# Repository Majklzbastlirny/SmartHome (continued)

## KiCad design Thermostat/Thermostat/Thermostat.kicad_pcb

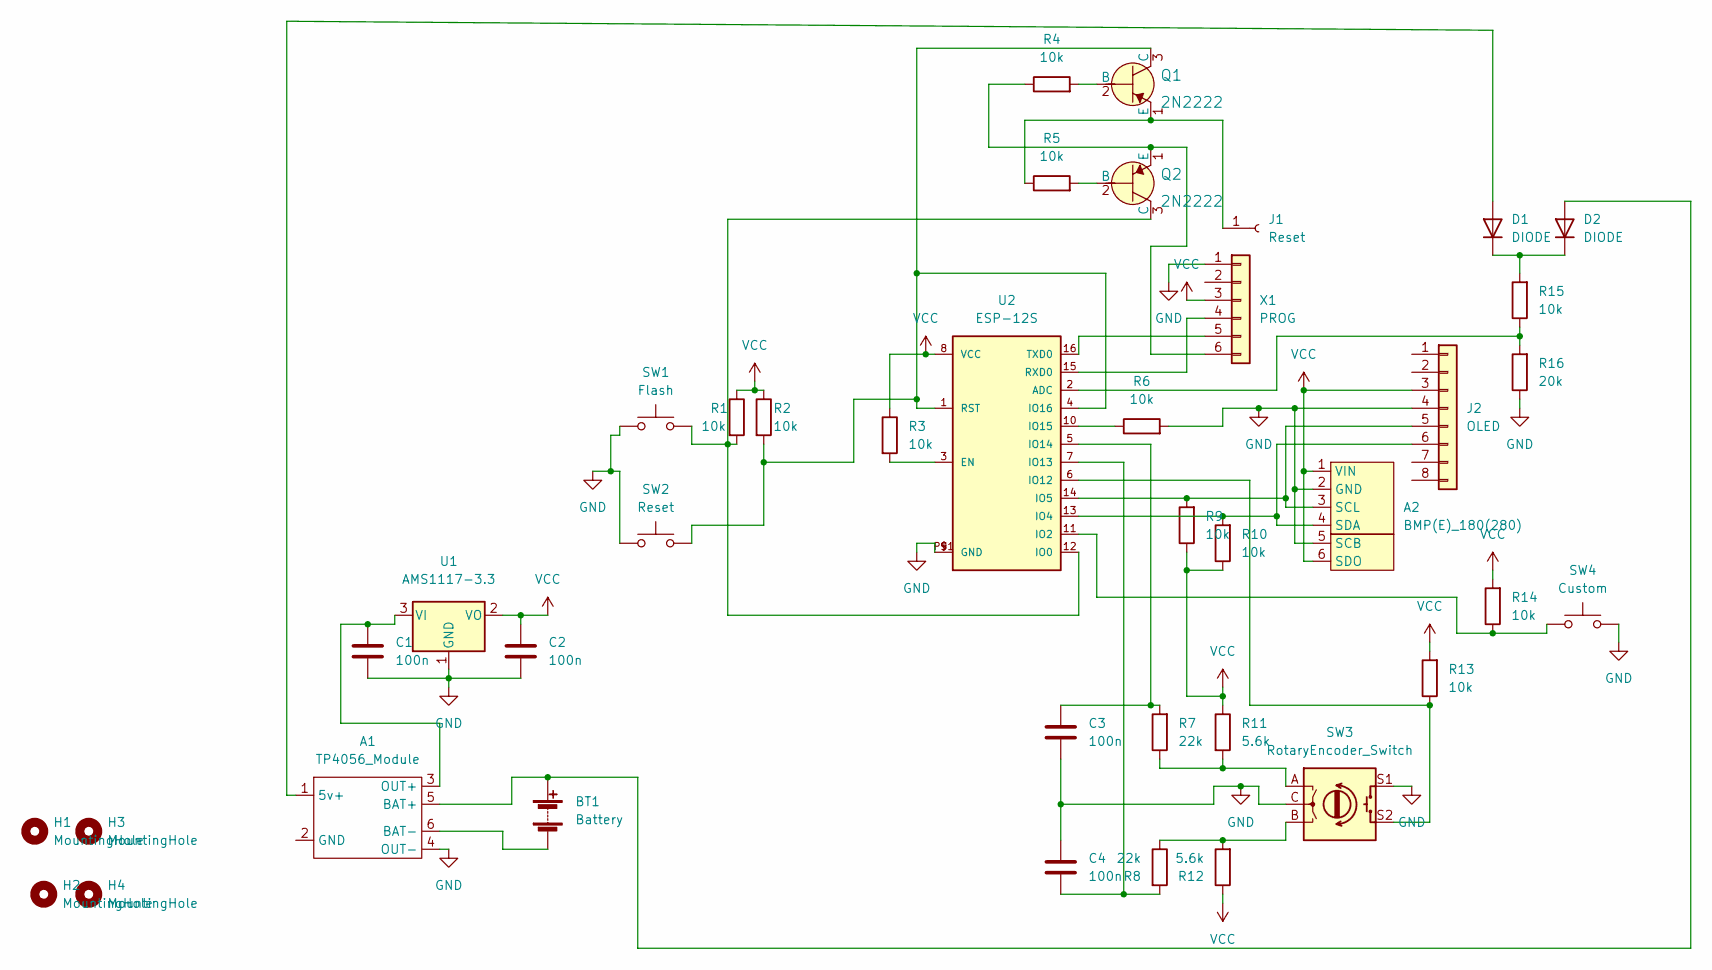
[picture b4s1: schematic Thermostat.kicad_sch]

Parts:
A1: TP4056_Module; TP4056-18650
A2: BMP(E)_180(280); PinHeader_1x06_P2.54mm_Vertical
BT1: Battery; BatteryHolder_MPD_BH-18650-PC2
C1, C2, C3, C4: 100n; C_Disc_D7.5mm_W2.5mm_P5.00mm
D1, D2: DIODE; D_DO-34_SOD68_P10.16mm_Horizontal
H1, H2, H3, H4: MountingHole; MountingHole_3.2mm_M3_DIN965_Pad_TopBottom
J1: Reset; PinHeader_1x01_P2.54mm_Vertical
J2: OLED; Adafruit_SSD1306
Q1, Q2: 2N2222; TO-18-3; MPN 2N2222; Digi-Key_PN 2N2222CS-ND
R1, R2, R3, R4, R5, R6, R9, R10, R13, R14, R15: 10k; R_Axial_DIN0207_L6.3mm_D2.5mm_P10.16mm_Horizontal
R7, R8: 22k; R_Axial_DIN0207_L6.3mm_D2.5mm_P10.16mm_Horizontal
R11, R12: 5.6k; R_Axial_DIN0207_L6.3mm_D2.5mm_P10.16mm_Horizontal
R16: 20k; R_Axial_DIN0207_L6.3mm_D2.5mm_P10.16mm_Horizontal
SW1: Flash; SW_PUSH_6mm
SW2: Reset; SW_PUSH_6mm
SW3: RotaryEncoder_Switch; RotaryEncoder_Alps_EC11E-Switch_Vertical_H20mm_CircularMoun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
SW4: Custom; SW_PUSH_6mm
U1: AMS1117-3.3; SOT-223-3_TabPin2
U2: ESP-12S
X1: PROG; PinHeader_1x06_P2.54mm_Vertical

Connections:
GND: A1.4 (OUT-), A2.2 (GND), A2.5 (SCB), C1.2, C2.2, C3.2, C4.1, J2.4, R6.2, R16.1, SW1.1, SW2.1, SW3.C, SW3.S1, SW4.2, U1.1 (GND), U2.9 (GND), U2.P$1 (GND), X1.1
unnamed: A1.1 (5v+), D1.1 (A)
unnamed: A1.3 (OUT+), C1.1, U1.3 (VI)
unnamed: A1.5 (BAT+), BT1.1 (+), D2.1 (A)
unnamed: A1.6 (BAT-), BT1.2 (-)
unnamed: A2.3 (SCL), J2.5, R9.2, U2.14 (IO5)
unnamed: A2.4 (SDA), J2.6, R10.2, U2.13 (IO4)
unnamed: C3.1, R7.2, U2.5 (IO14)
unnamed: C4.2, R8.2, U2.7 (IO13)
unnamed: D1.2 (K), D2.2 (K), R15.2
unnamed: J1.1, Q1.1 (E), R5.1
unnamed: Q1.2 (B), R4.2
unnamed: Q1.3 (C), R2.2, SW2.2, U2.1 (RST), U2.4 (IO16)
unnamed: Q2.1 (E), R4.1, X1.6
unnamed: Q2.2 (B), R5.2
unnamed: Q2.3 (C), R1.2, SW1.2, U2.12 (IO0)
unnamed: R3.2, U2.3 (EN)
unnamed: R6.1, U2.10 (IO15)
unnamed: R7.1, R11.2, SW3.A
unnamed: R8.1, R12.2, SW3.B
unnamed: R13.1, SW3.S2, U2.6 (IO12)
unnamed: R14.1, SW4.1, U2.11 (IO2)
unnamed: R15.1, R16.2, U2.2 (ADC)
unnamed: U2.15 (RXD0), X1.4
unnamed: U2.16 (TXD0), X1.5
VCC: A2.1 (VIN), A2.6 (SDO), C2.1, J2.3, R1.1, R2.1, R3.1, R9.1, R10.1, R11.1, R12.1, R13.2, R14.2, U1.2 (VO), U2.8 (VCC), X1.3

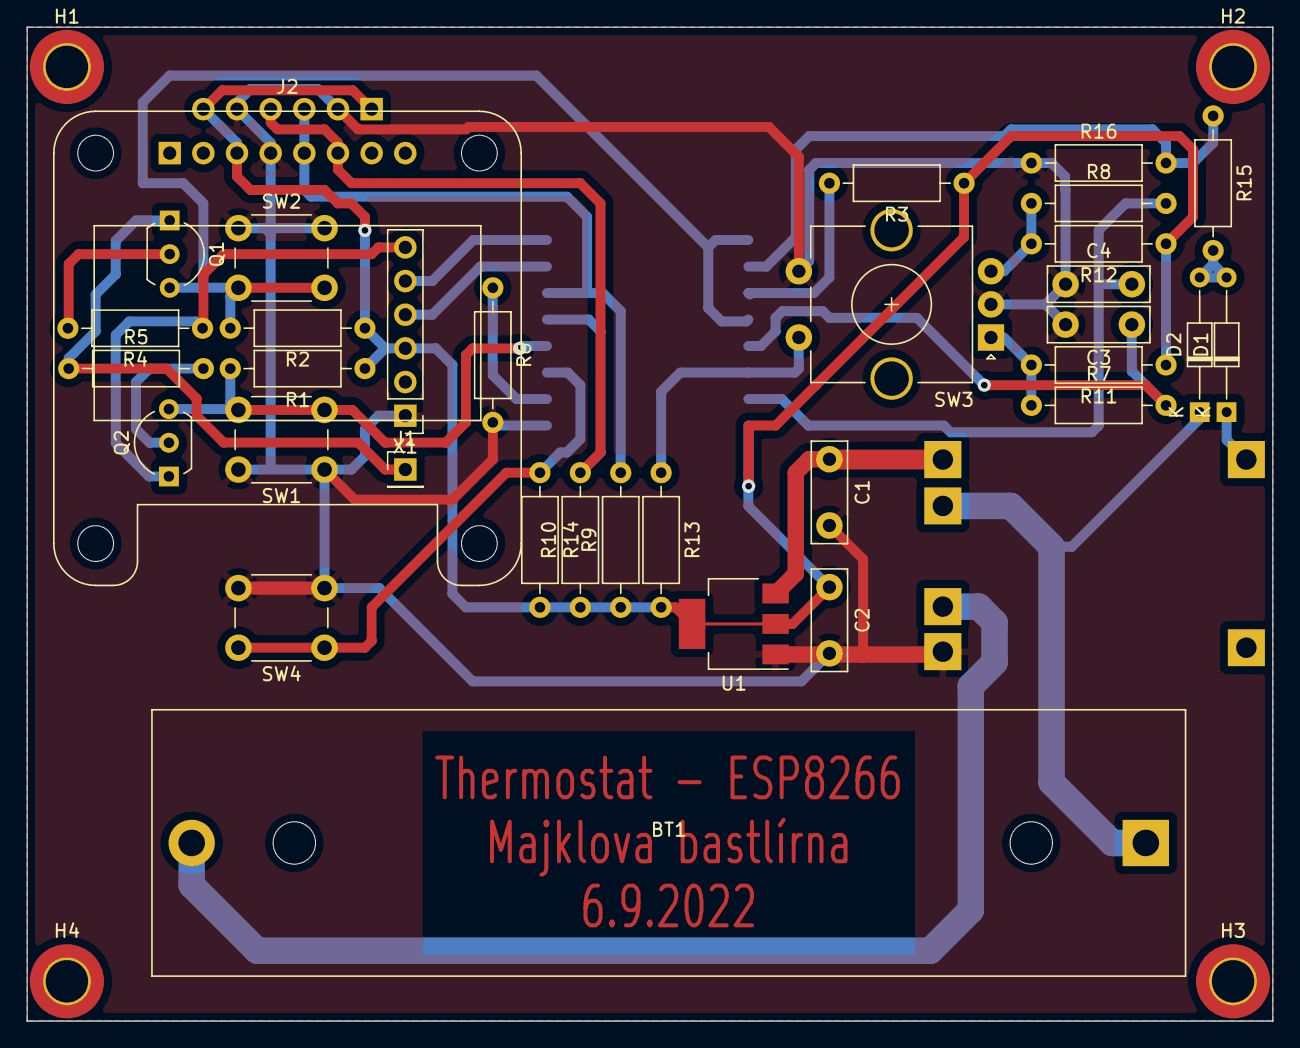
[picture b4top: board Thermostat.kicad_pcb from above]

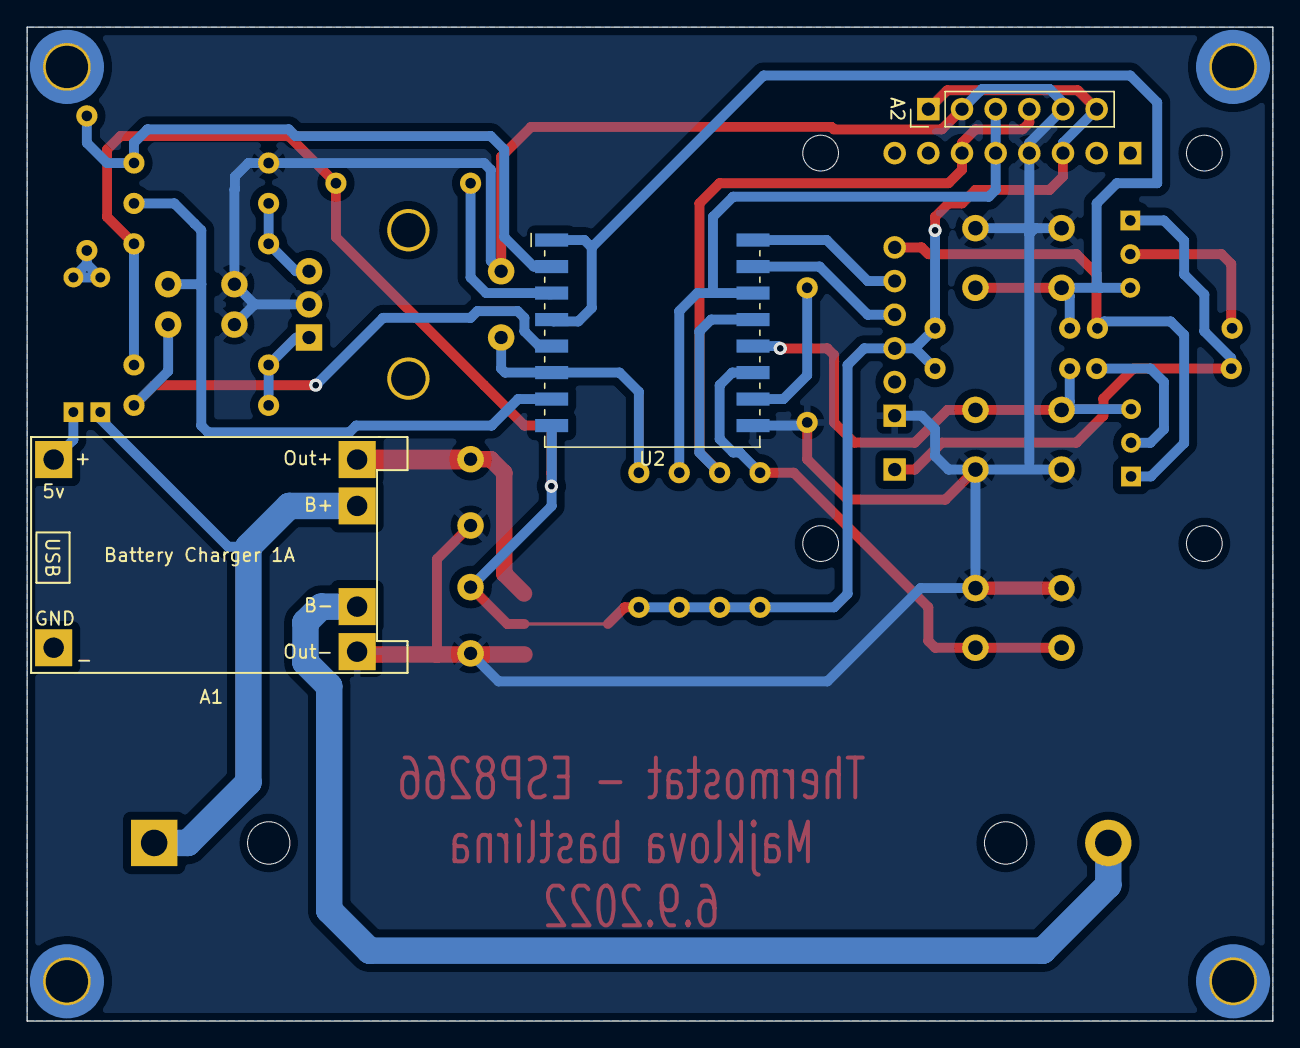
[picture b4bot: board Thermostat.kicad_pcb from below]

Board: 2 copper layers, 94.0 x 75.0 mm, 40 parts (3 on the bottom side), 26 nets.

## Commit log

2022-09-29 Push all
2022-10-04 kicad stuff
2022-10-04 many new features and some bugfixes
2023-01-04 New files
2023-01-12 added code
2023-01-13 First interactions with heater
2023-01-13 moved
2023-03-31 Gate opener added
